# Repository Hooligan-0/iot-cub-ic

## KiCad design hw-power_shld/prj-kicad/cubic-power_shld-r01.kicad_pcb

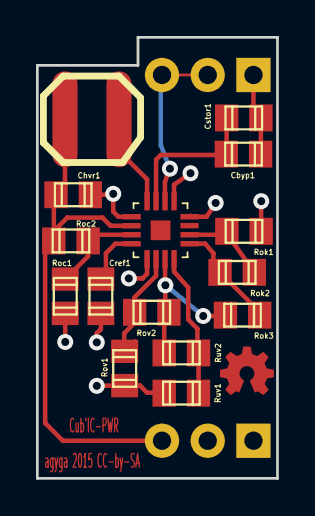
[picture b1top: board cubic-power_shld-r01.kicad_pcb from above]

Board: 2 copper layers, 13.3 x 24.5 mm, 16 parts (0 on the bottom side), 12 nets.

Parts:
Cbyp1: C; c_0805
Chvr1: C; c_0805
Cref1: C; c_0805
Cstor1: C; c_0805
PWR_OUT1: PWR; PWR_OUT
PwrIn1: BAT; PWR_IN
Roc1, Roc2: R; c_0805
Rok1, Rok2, Rok3: R; c_0805
Rov1, Rov2: R; c_0805
Ruv1, Ruv2: R; c_0805
bq25504_1: BQ25504; QFN16

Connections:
GND: Chvr1.1, Cref1.2, PWR_OUT1.6, Roc1.2, Rok1.2, Rov1.2, Ruv1.2, bq25504_1.1, bq25504_1.5, bq25504_1.12, bq25504_1.13
unnamed: Rov1.1, Rov2.2, bq25504_1.6
unnamed: PwrIn1.3, PwrIn1.9, bq25504_1.14
unnamed: Rok1.1, Rok2.1, bq25504_1.10
unnamed: Rok2.2, Rok3.1, bq25504_1.9
unnamed: Ruv1.1, Ruv2.2, bq25504_1.8
unnamed: Rok3.2, Rov2.1, Ruv2.1, bq25504_1.7
unnamed: Roc1.1, Roc2.2, bq25504_1.3
unnamed: Cbyp1.2, Cstor1.2, PwrIn1.4
unnamed: Cbyp1.1, Cstor1.1, bq25504_1.15
unnamed: Cref1.1, bq25504_1.4
unnamed: Chvr1.2, PWR_OUT1.5, Roc2.1, bq25504_1.2

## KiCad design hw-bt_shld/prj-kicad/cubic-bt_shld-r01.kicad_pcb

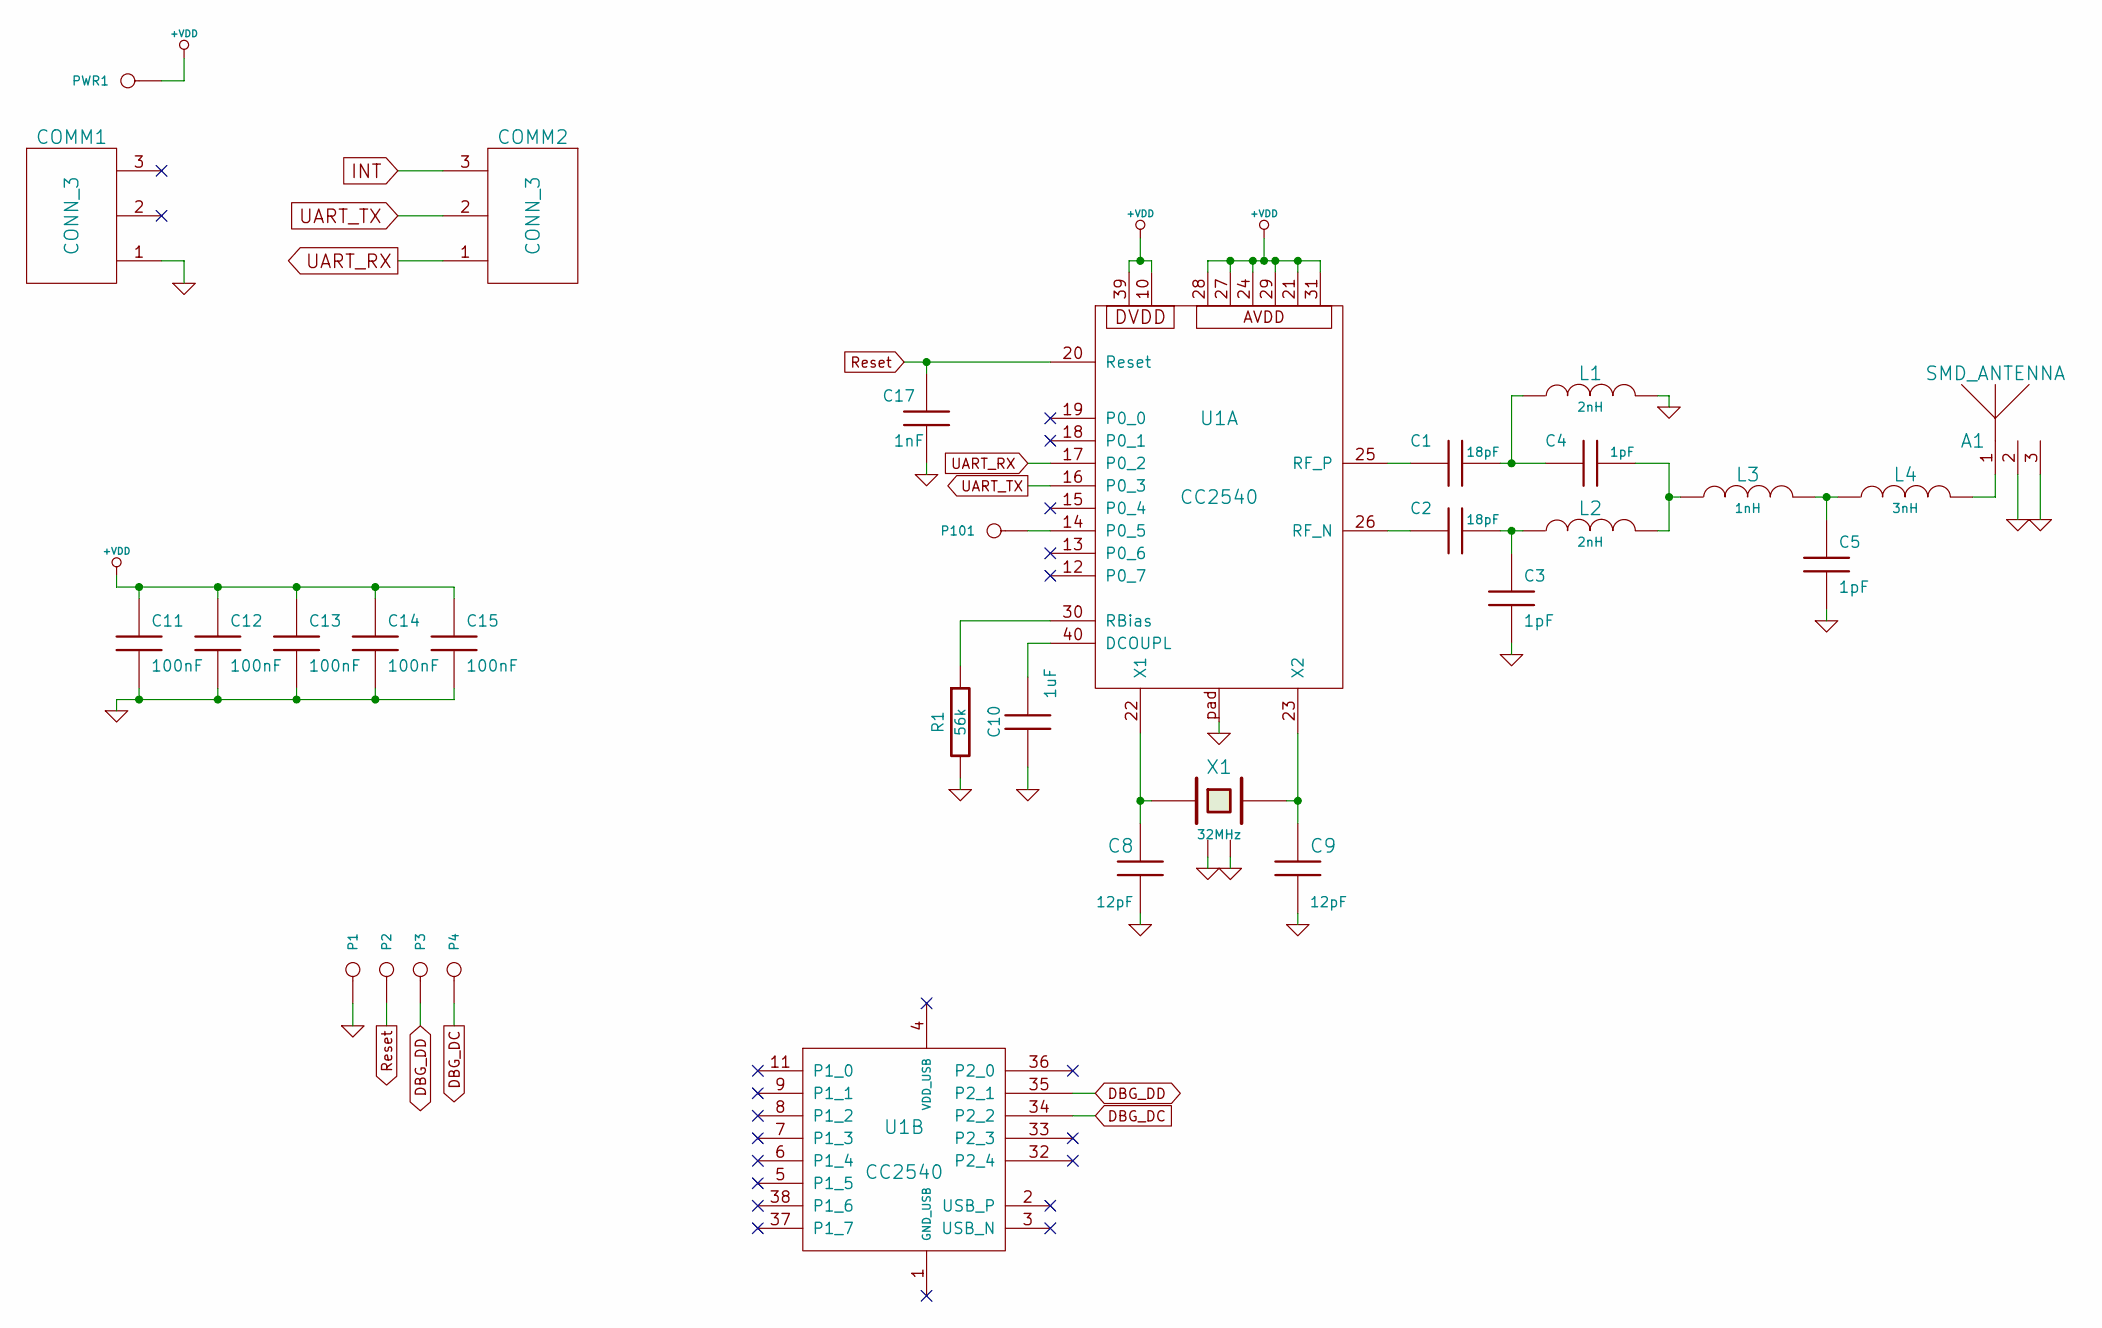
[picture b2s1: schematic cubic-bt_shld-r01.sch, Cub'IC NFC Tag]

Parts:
A1: SMD_ANTENNA
C1, C2: 18pF
C3, C4, C5: 1pF
C8, C9: 12pF
C10: 1uF
C11, C12, C13, C14, C15: 100nF
C17: 1nF
COMM1, COMM2: CONN_3
L1, L2: 2nH
L3: 1nH
L4: 3nH
P1, P2, P3, P4, P101: CONN_1
PWR1: CONN_1
R1: 56k
U1: CC2540
X1: 32MHz

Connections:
+VDD: C11.1, C12.1, C13.1, C14.1, C15.1, PWR1.1, U1.10, U1.21, U1.24, U1.27, U1.28, U1.29, U1.31, U1.39
DBG_DC: P4.1, U1.34 (P2_2)
DBG_DD: P3.1, U1.35 (P2_1)
GND: A1.2, A1.3, C3.2, C5.2, C8.2, C9.2, C10.2, C11.2, C12.2, C13.2, C14.2, C15.2, C17.2, COMM1.1, L1.2, P1.1, R1.2, U1.pad, X1.2, X1.4
INT: COMM2.3
unnamed: P101.1, U1.14 (P0_5)
unnamed: C10.1, U1.40 (DCOUPL)
unnamed: C2.1, U1.26 (RF_N)
unnamed: C1.1, U1.25 (RF_P)
unnamed: C2.2, C3.1, L2.1
unnamed: C9.1, U1.23 (X2), X1.3
unnamed: R1.1, U1.30 (RBias)
unnamed: C8.1, U1.22 (X1), X1.1
unnamed: C5.1, L3.2, L4.1
unnamed: C4.2, L2.2, L3.1
unnamed: C1.2, C4.1, L1.1
unnamed: A1.1, L4.2
Reset: C17.1, P2.1, U1.20 (Reset)
UART_RX: COMM2.1, U1.17 (P0_2)
UART_TX: COMM2.2, U1.16 (P0_3)

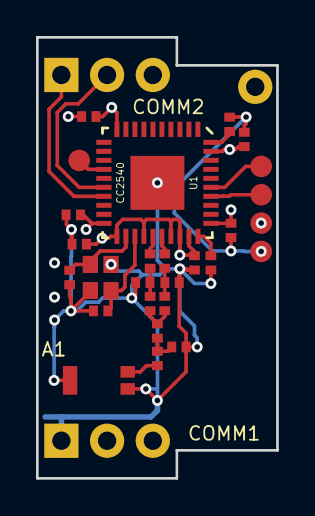
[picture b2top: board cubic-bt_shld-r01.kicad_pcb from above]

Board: 4 copper layers, 13.3 x 24.5 mm, 30 parts (0 on the bottom side), 19 nets.

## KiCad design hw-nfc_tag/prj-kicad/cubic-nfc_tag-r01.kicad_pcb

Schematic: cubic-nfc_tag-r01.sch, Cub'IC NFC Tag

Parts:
BT1, BT2: BATTERY
COMM1, COMM2: CONN_3
P1, P2, P3, P4, P5, P6, P9: CONN_1
U1: M24LR04E

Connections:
+VHvst: P5.1, U1.1 (Vout)
GND: COMM1.1, P6.1, U1.4
I2C_SCL: COMM1.3, U1.6 (SCL)
I2C_SDA: COMM1.2, U1.5 (SDA)
unnamed: BT2.1 (+), P9.1
unnamed: P1.1, U1.8
unnamed: BT1.2 (-), BT2.2 (-), P4.1
unnamed: U1.2 (AC0), U1.3 (AC1)
unnamed: BT1.1 (+), P3.1

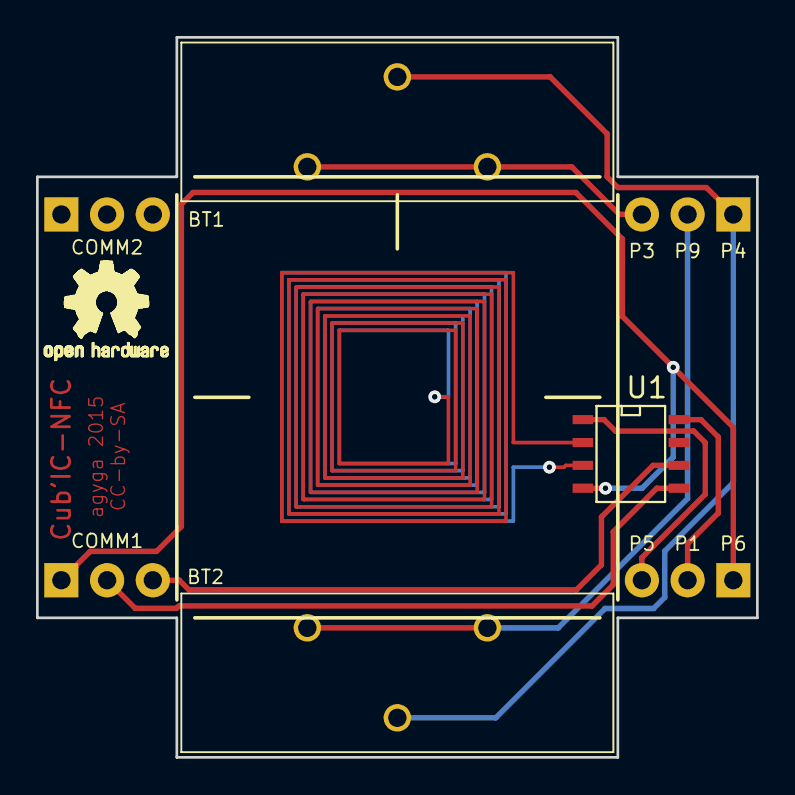
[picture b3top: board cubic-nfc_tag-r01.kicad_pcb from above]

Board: 2 copper layers, 40.0 x 40.0 mm, 12 parts (0 on the bottom side), 9 nets.

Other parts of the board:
ohw_logo: VAL**; ohw_logo

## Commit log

2015-07-04 = ADD: PCB for NFC layer and battery holders
2015-07-06 = ADD: Template for power daughterboard
2015-07-10 = UPD: Move ground pad and add a second communication port
2015-07-11 = ADD: Create a new shield for Bluetooth communication
2015-07-13 launch power shld project
2015-07-13 add footprint and label place netlist todo : brd
2015-07-14 ajout gitignore
2015-07-14 remove backup file
2015-07-14 correction erreur symbole masse placement des composants
2015-07-14 gnd done
2015-07-14 routage fini
2015-07-14 route modifiées en fonction des infos de Hooli
2015-07-15 move some R move reference
2015-07-15 missing a net
2015-07-15 change footprint qfn and re-route
2015-07-15 add GND plan.
2015-07-15 multiple 'bug' report correction
2015-07-15 modify gnd
2015-07-16 move text and add logo
2015-07-16 add logo and move txt
2015-07-18 = UPD: Insert CC2540 and the HF interface to antenna

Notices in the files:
hw-nfc_tag/prj-kicad/cubic-nfc_tag-r01.kicad_pcb:
CC-by-SA
hw-power_shld/prj-kicad/cubic-power_shld-r01.kicad_pcb:
agyga 2015 CC-by-SA
